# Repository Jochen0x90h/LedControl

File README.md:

# LED Control

Control unit for LED strips

## Features
* 128x64 OLED Display
* Support for presets, i.e. the same effect can be configured with different parameters in the preset list

## Compile
See README.md of coco base library

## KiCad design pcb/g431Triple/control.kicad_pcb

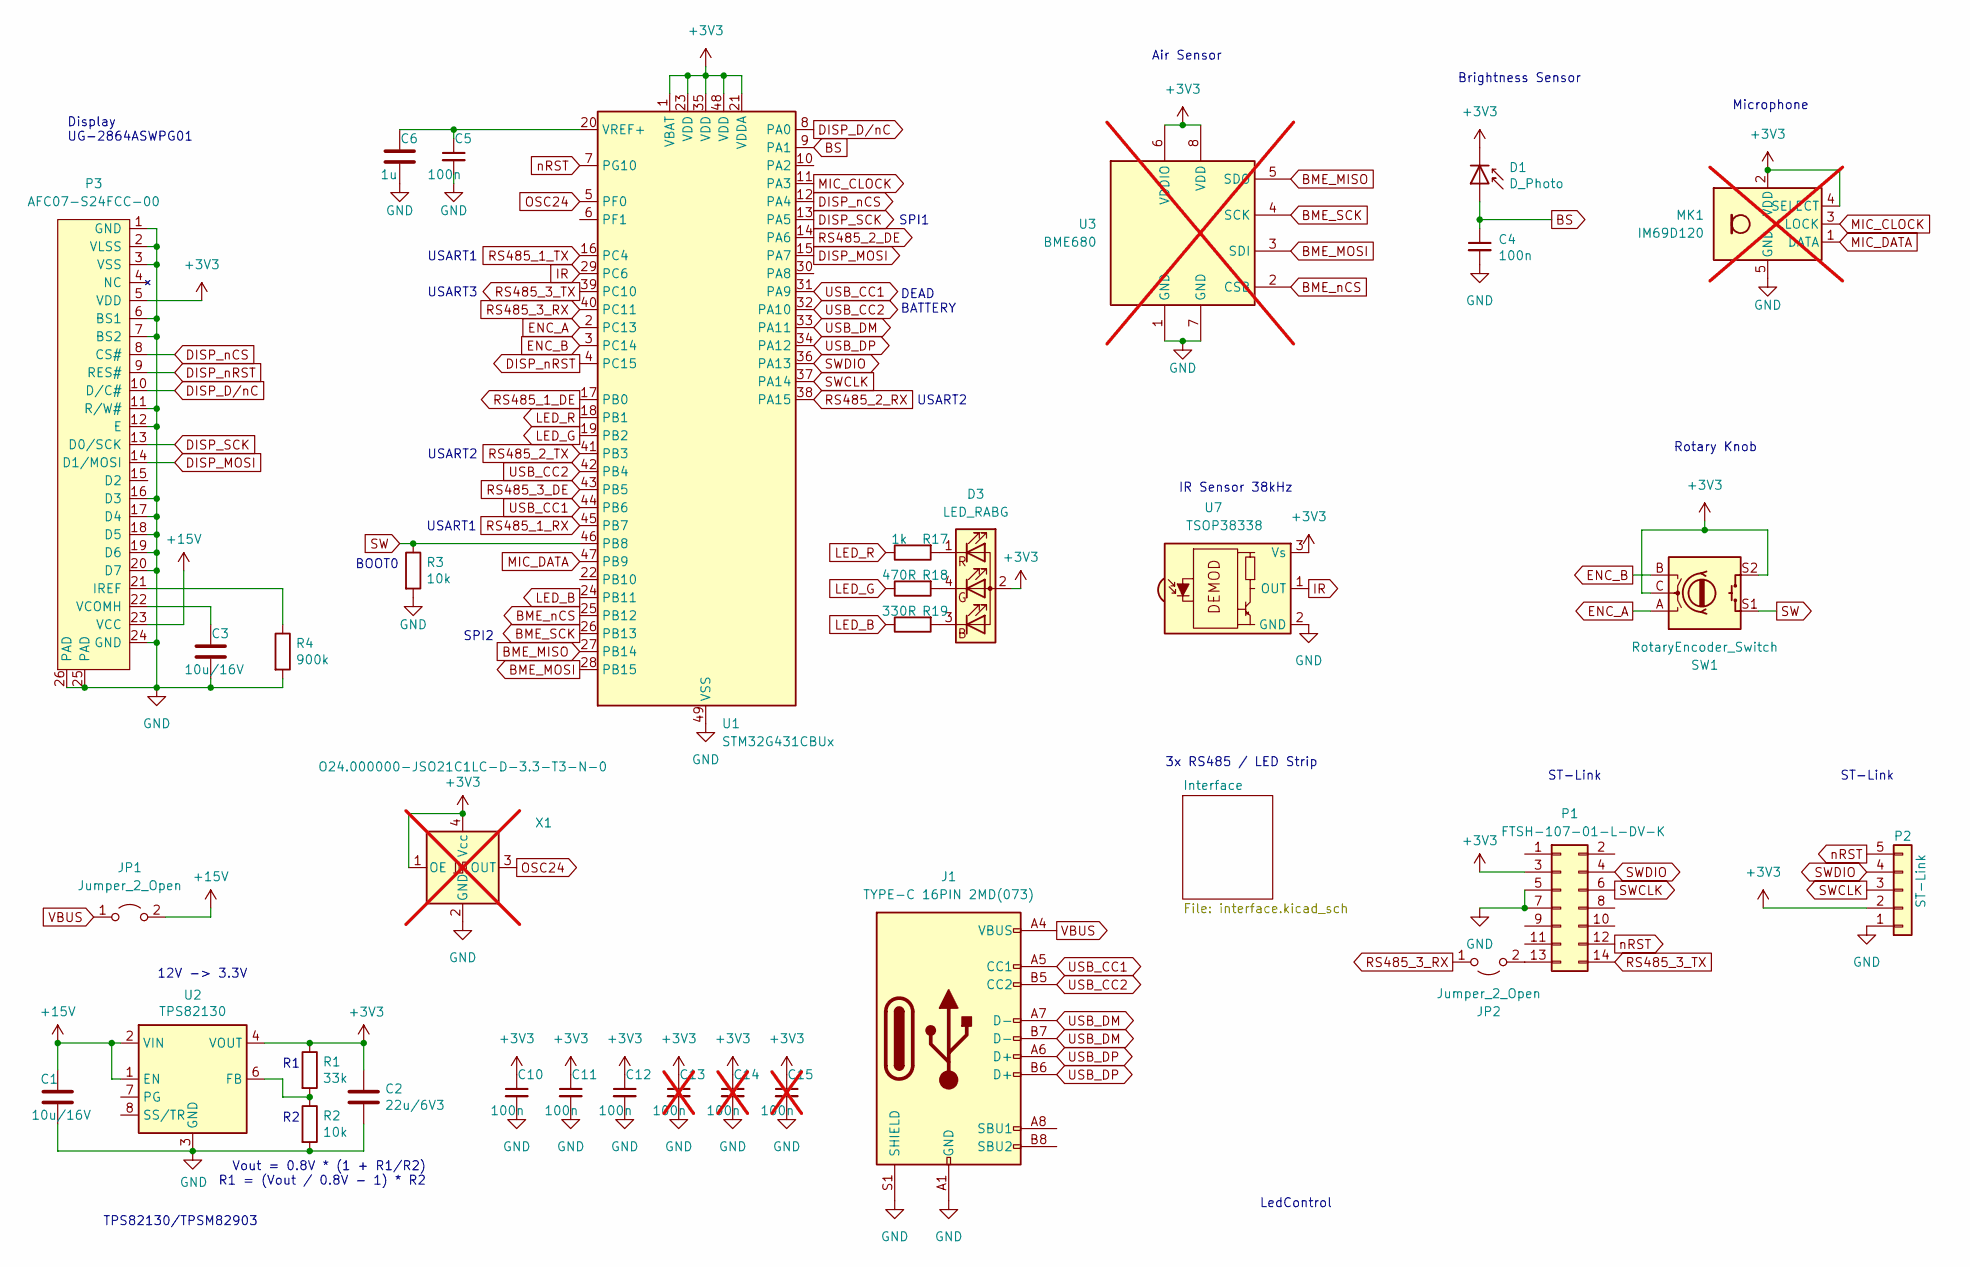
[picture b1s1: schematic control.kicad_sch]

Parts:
C1, C3: 10u/16V; 1206
C2: 22u/6V3; 0805
C4, C5, C10, C11, C12: 100n; 0603
C6: 1u; 0603
C13, C14, C15: 100n; 0603; not fitted
D1: D_Photo; PhotoDiode
D3: LED_RABG; LED_D5.0mm-4_RGB
J1: TYPE-C 16PIN 2MD(073); TYPE-C-16PIN-2MD-073
JP1, JP2: Jumper_2_Open; Jumper
MK1: IM69D120; Infineon_PG-LLGA-5-1; not fitted
P1: FTSH-107-01-L-DV-K; PinHeader-2x7-1.27mm-smd
P2: ST-Link; ProgPads
P3: AFC07-S24FCC-00; Connector-Flat-24-0.5mm
R1: 33k; 0603
R2, R3: 10k; 0603
R4: 900k; 0603
R17: 1k; 0603
R18: 470R; 0603
R19: 330R; 0603
SW1: RotaryEncoder_Switch; PEC12R-4217F-S0024
U1: STM32G431CBUx; STM32-UFQFPN48
U2: TPS82130
U3: BME680; not fitted
U7: TSOP38338
X1: O24.000000-JSO21C1LC-D-3.3-T3-N-0; JSO21; not fitted

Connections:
+3V3: C2.1, C10.1, C11.1, C12.1, C13.1, C14.1, C15.1, D1.1 (K), D3.2 (A), MK1.2 (VDD), MK1.4 (SELECT), P1.3, P2.2, P3.5 (VDD), R1.1, SW1.C, SW1.S2, U1.1 (VBAT), U1.21 (VDDA), U1.23 (VDD), U1.35 (VDD), U1.48 (VDD), U2.4 (VOUT), U2.5 (VOUT), U3.6 (VDDIO), U3.8 (VDD), U7.3 (Vs), X1.1 (OE), X1.4 (Vcc); also elsewhere on the board
+15V: C1.1, JP1.2 (B), P3.23 (VCC), U2.1 (EN), U2.2 (VIN); also elsewhere on the board
BME_MISO: U1.27 (PB14), U3.5 (SDO)
BME_MOSI: U1.28 (PB15), U3.3 (SDI)
BME_SCK: U1.26 (PB13), U3.4 (SCK)
BME_nCS: U1.25 (PB12), U3.2 (CSB)
BS: C4.1, D1.2 (A), U1.9 (PA1)
DISP_D/nC: P3.10 (D/C#), U1.8 (PA0)
DISP_MOSI: P3.14 (D1/MOSI), U1.15 (PA7)
DISP_SCK: P3.13 (D0/SCK), U1.13 (PA5)
DISP_nCS: P3.8 (CS#), U1.12 (PA4)
DISP_nRST: P3.9 (RES#), U1.4 (PC15)
ENC_A: SW1.A, U1.2 (PC13)
ENC_B: SW1.B, U1.3 (PC14)
GND: C1.2, C2.2, C3.2, C4.2, C5.2, C6.2, C10.2, C11.2, C12.2, C13.2, C14.2, C15.2, J1.A1 (GND), J1.A12 (GND), J1.B1 (GND), J1.B12 (GND), J1.S1 (SHIELD), MK1.5 (GND), P1.5, P1.7, P2.1, P3.1 (GND), P3.2 (VLSS), P3.3 (VSS), P3.6 (BS1), P3.7 (BS2), P3.11 (R/W#), P3.12 (E), P3.16 (D3), P3.17 (D4), P3.18 (D5), P3.19 (D6), P3.20 (D7), P3.24 (GND), P3.25 (PAD), P3.26 (PAD), R2.2, R3.2, R4.2, U1.49 (VSS), U2.3 (GND), U2.9 (GND), U3.1 (GND), U3.7 (GND), U7.2 (GND), X1.2 (GND); also elsewhere on the board
IR: U1.29 (PC6), U7.1 (OUT)
LED_B: R19.1, U1.24 (PB11)
LED_G: R18.1, U1.19 (PB2)
LED_R: R17.1, U1.18 (PB1)
MIC_CLOCK: MK1.3 (CLOCK), U1.11 (PA3)
MIC_DATA: MK1.1 (DATA), U1.47 (PB9)
unnamed: D3.3 (BK), R19.2
unnamed: D3.4 (GK), R18.2
unnamed: D3.1 (RK), R17.2
unnamed: JP2.2 (B), P1.13
unnamed: P3.21 (IREF), R4.1
unnamed: C3.1, P3.22 (VCOMH)
unnamed: C5.1, C6.1, U1.20 (VREF+)
unnamed: R1.2, R2.1, U2.6 (FB)
OSC24: U1.5 (PF0), X1.3 (OUT)
RS485_1_DE: U1.17 (PB0); also elsewhere on the board
RS485_1_RX: U1.45 (PB7); also elsewhere on the board
RS485_1_TX: U1.16 (PC4); also elsewhere on the board
RS485_2_DE: U1.14 (PA6); also elsewhere on the board
RS485_2_RX: U1.38 (PA15); also elsewhere on the board
RS485_2_TX: U1.41 (PB3); also elsewhere on the board
RS485_3_DE: U1.43 (PB5); also elsewhere on the board
RS485_3_RX: JP2.1 (A), U1.40 (PC11); also elsewhere on the board
RS485_3_TX: P1.14, U1.39 (PC10); also elsewhere on the board
SW: R3.1, SW1.S1, U1.46 (PB8)
SWCLK: P1.6, P2.3, U1.37 (PA14)
SWDIO: P1.4, P2.4, U1.36 (PA13)
USB_CC1: J1.A5 (CC1), U1.31 (PA9), U1.44 (PB6)
USB_CC2: J1.B5 (CC2), U1.32 (PA10), U1.42 (PB4)
USB_DM: J1.A7 (D-), J1.B7 (D-), U1.33 (PA11)
USB_DP: J1.A6 (D+), J1.B6 (D+), U1.34 (PA12)
VBUS: J1.A4 (VBUS), J1.A9 (VBUS), J1.B4 (VBUS), J1.B9 (VBUS), JP1.1 (A)
nRST: P1.12, P2.5, U1.7 (PG10)

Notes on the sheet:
12V -> 3.3V
BOOT0
SPI2
USART2
ST-Link
Vout = 0.8V * (1 + R1/R2) R1 = (Vout / 0.8V - 1) * R2
DEAD BATTERY
Display UG-2864ASWPG01
Air Sensor
USART3
Microphone
LedControl
3x RS485 / LED Strip
USART1
Brightness Sensor
TPS82130/TPSM82903
IR Sensor 38kHz
SPI1
Rotary Knob

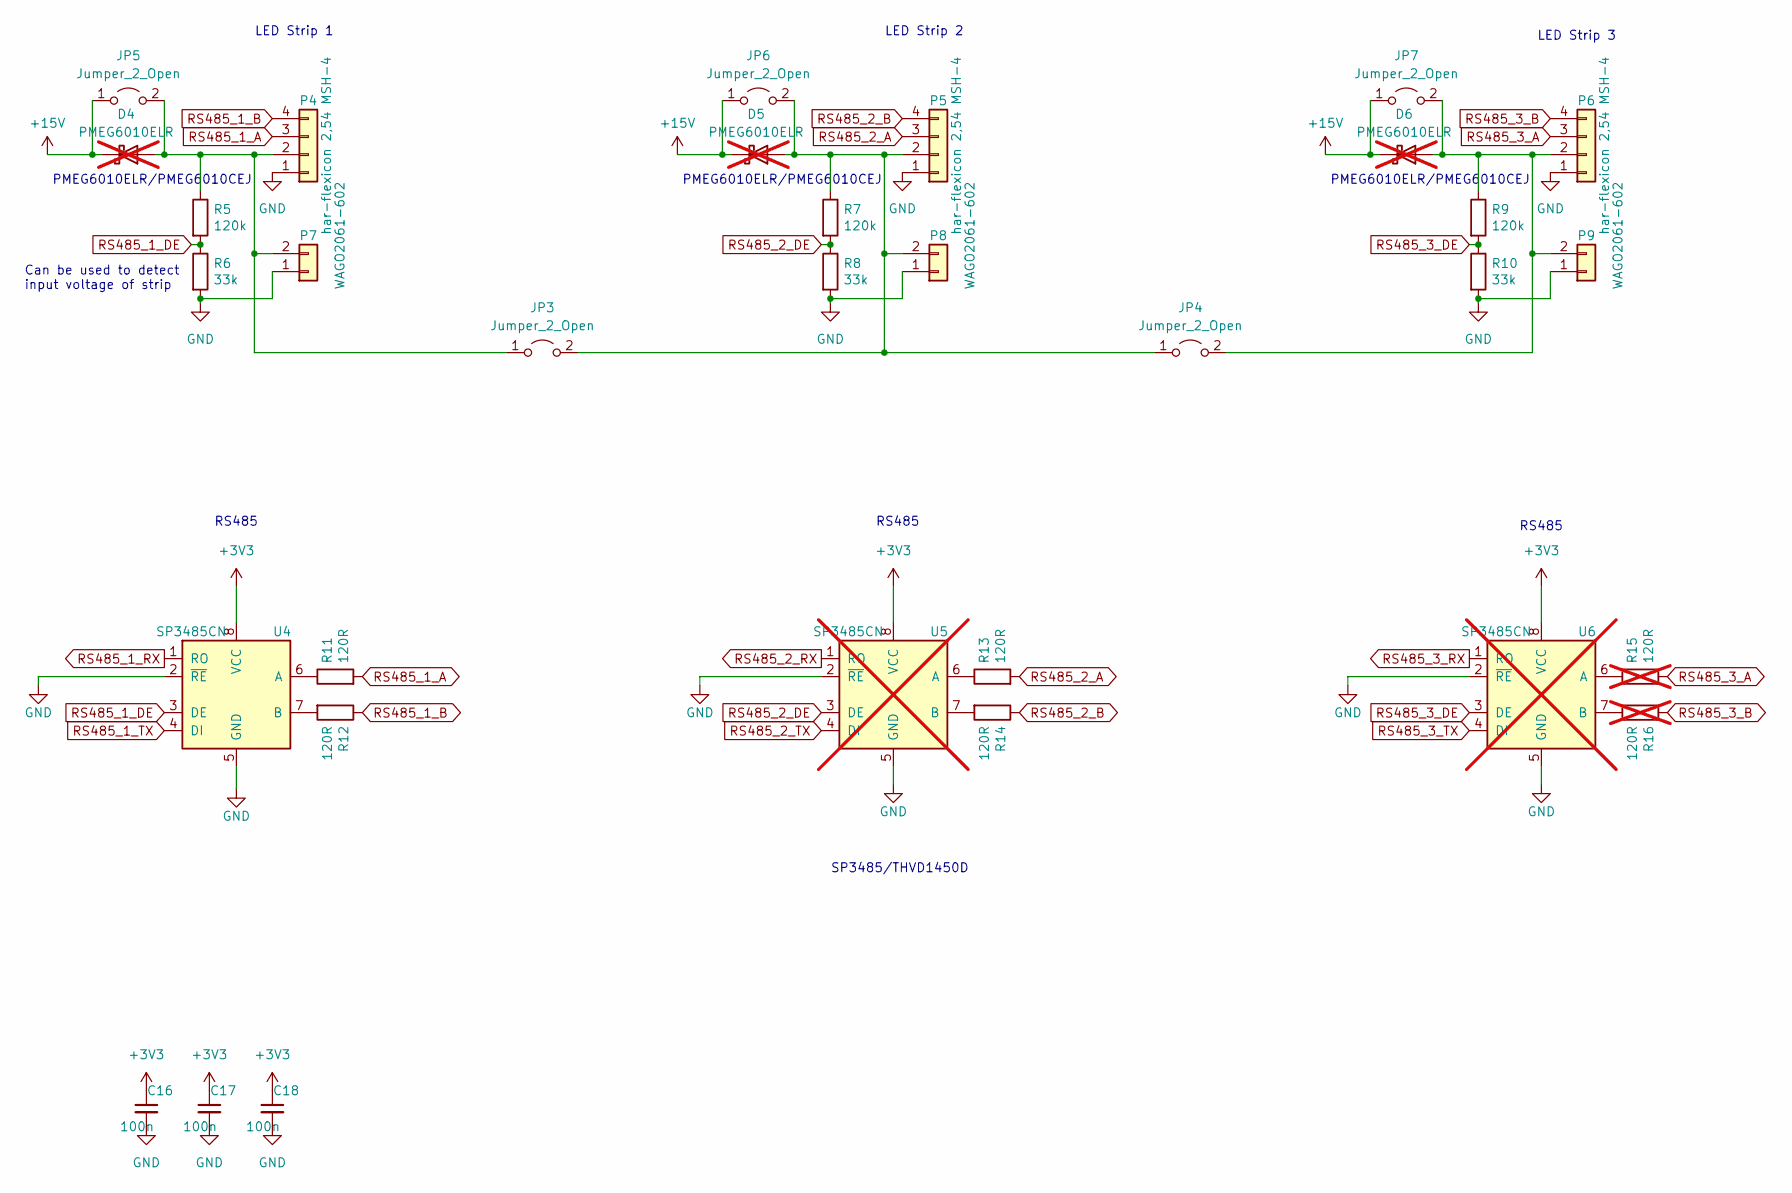
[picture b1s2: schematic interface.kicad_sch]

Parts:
C16, C17, C18: 100n; 0603
D4, D5, D6: PMEG6010ELR; not fitted
JP3, JP4, JP5, JP6, JP7: Jumper_2_Open; Jumper
P4, P5, P6: har-flexicon 2,54 MSH-4; Harting14110413002000
P7, P8, P9: WAGO2061-602
R5, R7, R9: 120k; 0603
R6, R8, R10: 33k; 0603
R11, R12, R13, R14: 120R; 1206-term
R15, R16: 120R; 1206-term; not fitted
U4: SP3485CN; SO-8
U5, U6: SP3485CN; SO-8; not fitted

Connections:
+3V3: C16.1, C17.1, C18.1, U4.8 (VCC), U5.8 (VCC), U6.8 (VCC); also elsewhere on the board
+15V: D4.1 (K), D5.1 (K), D6.1 (K), JP5.1 (A), JP6.1 (A), JP7.1 (A); also elsewhere on the board
GND: C16.2, C17.2, C18.2, P4.1, P5.1, P6.1, P7.1, P8.1, P9.1, R6.2, R8.2, R10.2, U4.2 (~RE), U4.5 (GND), U5.2 (~RE), U5.5 (GND), U6.2 (~RE), U6.5 (GND); also elsewhere on the board
unnamed: D4.2 (A), JP3.1 (A), JP5.2 (B), P4.2, P7.2, R5.1
unnamed: D5.2 (A), JP3.2 (B), JP4.1 (A), JP6.2 (B), P5.2, P8.2, R7.1
unnamed: D6.2 (A), JP4.2 (B), JP7.2 (B), P6.2, P9.2, R9.1
unnamed: R11.1, U4.6 (A)
unnamed: R12.2, U4.7 (B)
unnamed: R13.1, U5.6 (A)
unnamed: R14.2, U5.7 (B)
unnamed: R15.1, U6.6 (A)
unnamed: R16.2, U6.7 (B)
RS485_1_A: P4.3, R11.2
RS485_1_B: P4.4, R12.1
RS485_1_DE: R5.2, R6.1, U4.3 (DE); also elsewhere on the board
RS485_1_RX: U4.1 (RO); also elsewhere on the board
RS485_1_TX: U4.4 (DI); also elsewhere on the board
RS485_2_A: P5.3, R13.2
RS485_2_B: P5.4, R14.1
RS485_2_DE: R7.2, R8.1, U5.3 (DE); also elsewhere on the board
RS485_2_RX: U5.1 (RO); also elsewhere on the board
RS485_2_TX: U5.4 (DI); also elsewhere on the board
RS485_3_A: P6.3, R15.2
RS485_3_B: P6.4, R16.1
RS485_3_DE: R9.2, R10.1, U6.3 (DE); also elsewhere on the board
RS485_3_RX: U6.1 (RO); also elsewhere on the board
RS485_3_TX: U6.4 (DI); also elsewhere on the board

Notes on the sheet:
Can be used to detect input voltage of strip
LED Strip 3
PMEG6010ELR/PMEG6010CEJ
LED Strip 1
SP3485/THVD1450D
LED Strip 2
RS485

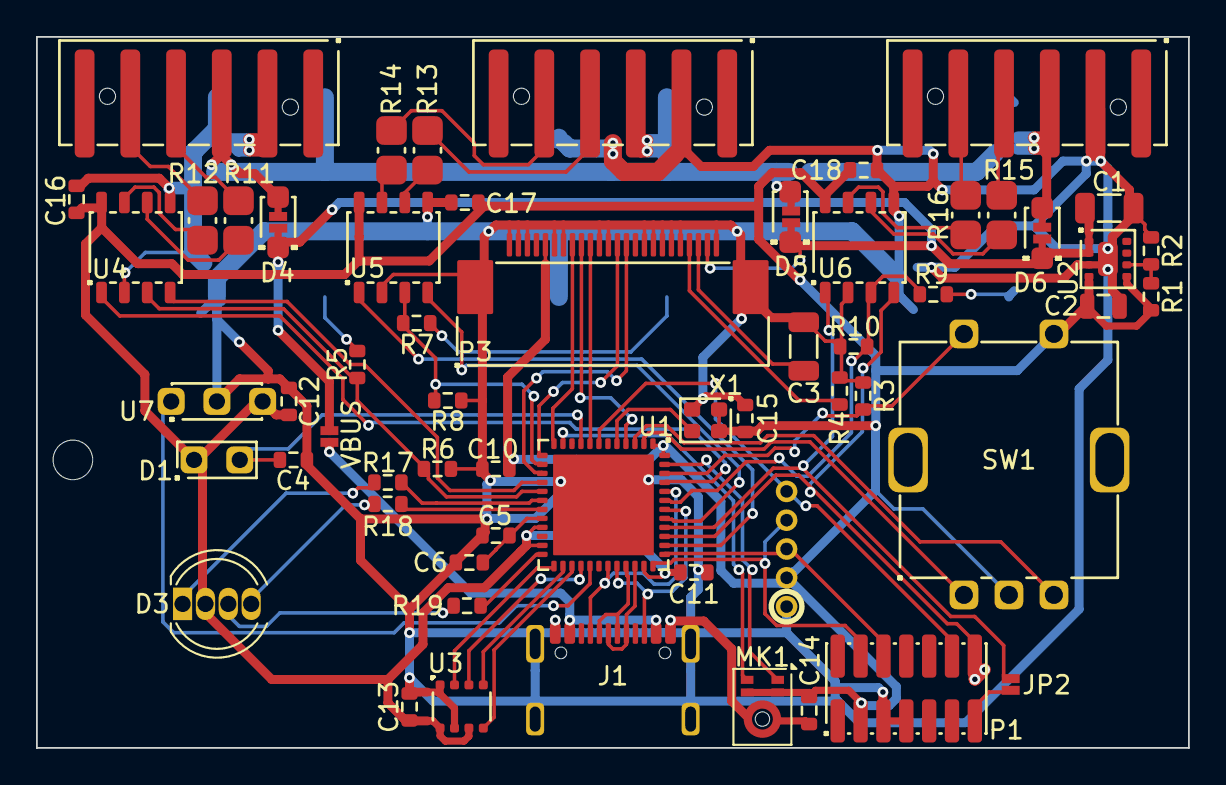
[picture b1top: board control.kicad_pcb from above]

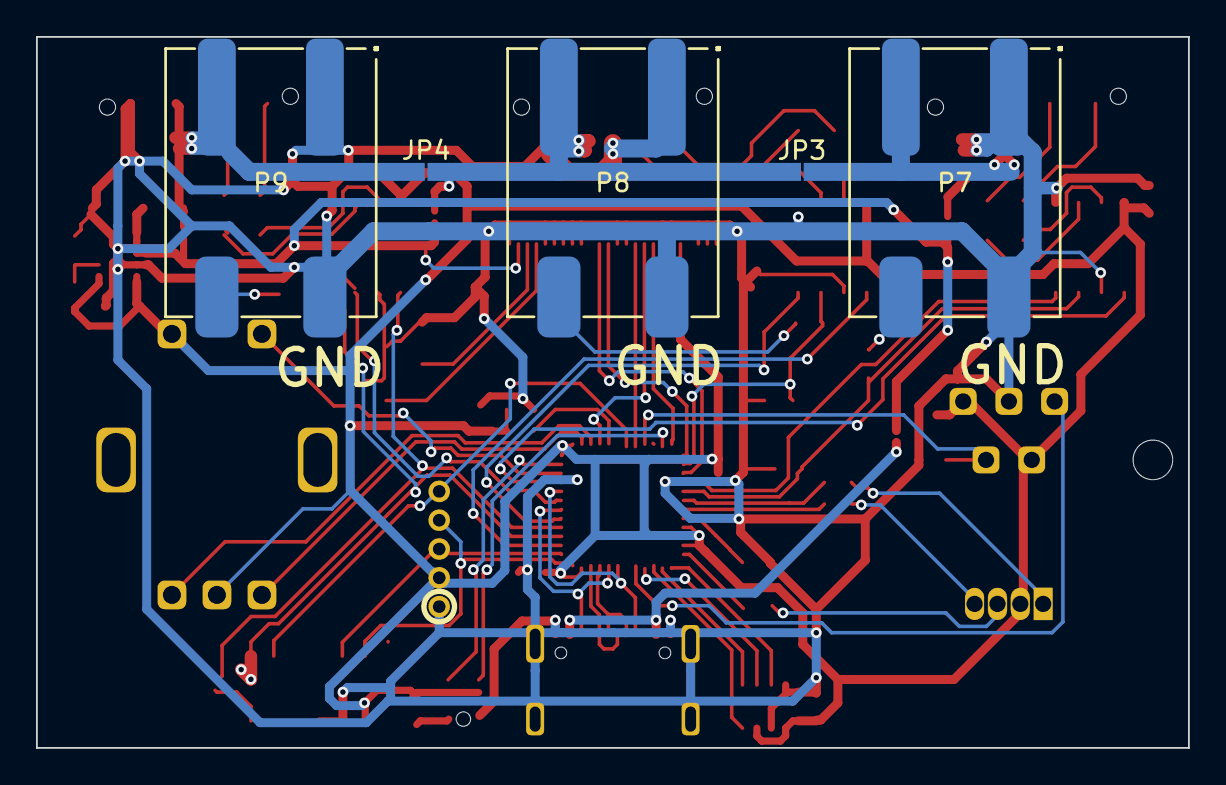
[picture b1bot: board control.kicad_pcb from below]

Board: 2 copper layers, 64.0 x 39.5 mm, 66 parts (6 on the bottom side), 63 nets.

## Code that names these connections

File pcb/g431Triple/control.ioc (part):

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Mcu.Name=STM32G431C(6-8-B)Ux
Mcu.Package=UFQFPN48
Mcu.UserName=STM32G431CBUx
PA0.GPIOParameters=GPIO_Label
PA0.GPIO_Label=DISP_D/C\#
PA0.Signal=GPIO_Output
PA1.Mode=INP
PA1.Signal=COMP1_INP
PA10.Mode=EnableDeadBattery
PA10.Signal=UCPD1_DBCC2
PA11.Mode=Device
PA11.Signal=USB_DM
PA12.Mode=Device
PA12.Signal=USB_DP
PA13.Mode=Serial_Wire
PA13.Signal=SYS_JTMS-SWDIO
PA14.Mode=Serial_Wire
PA14.Signal=SYS_JTCK-SWCLK
PA15.Mode=Asynchronous
PA15.Signal=USART2_RX
PA2.Mode=Follower-DAC_OUT2-INP
PA2.Signal=OPAMP1_VOUT
PA3.Signal=SAI1_CK1
PA4.GPIOParameters=GPIO_Label
PA4.GPIO_Label=DISP_CS
PA4.Signal=GPIO_Output
PA5.Mode=TX_Only_Simplex_Unidirect_Master
PA5.Signal=SPI1_SCK
PA6.GPIOParameters=GPIO_Label
PA6.GPIO_Label=RS485_2_DE
PA6.Signal=GPIO_Output
PA7.Mode=TX_Only_Simplex_Unidirect_Master
PA7.Signal=SPI1_MOSI
PA9.Mode=EnableDeadBattery
PA9.Signal=UCPD1_DBCC1
PB0.GPIOParameters=GPIO_Label
PB0.GPIO_Label=RS485_DE
PB0.Signal=GPIO_Output
PB1.Mode=Standalone-DAC_OUT2-INP
PB1.Signal=OPAMP3_VOUT
PB12.GPIOParameters=GPIO_Label
PB12.GPIO_Label=BME_CS
PB12.Signal=GPIO_Output
PB13.Mode=Full_Duplex_Master
PB13.Signal=SPI2_SCK
PB14.Mode=Full_Duplex_Master
PB14.Signal=SPI2_MISO
PB15.Mode=Full_Duplex_Master
PB15.Signal=SPI2_MOSI
PB2.Mode=Standalone-DAC_OUT2-INP
PB2.Signal=OPAMP3_VINM
PB3.Mode=Asynchronous
PB3.Signal=USART2_TX
PB4.Mode=Sink_AllSignals
PB4.Signal=UCPD1_CC2
PB5.GPIOParameters=GPIO_Label
PB5.GPIO_Label=RS485_3_DE
PB5.Signal=GPIO_Output
PB6.Mode=Sink_AllSignals
PB6.Signal=UCPD1_CC1
PB7.Mode=Asynchronous
PB7.Signal=USART1_RX
PB8-BOOT0.GPIOParameters=GPIO_Label
PB8-BOOT0.GPIO_Label=SW
PB8-BOOT0.Signal=GPIO_Input
PB9.Signal=SAI1_D2
PC10.Mode=Asynchronous
PC10.Signal=USART3_TX
PC11.Mode=Asynchronous
PC11.Signal=USART3_RX
PC13.GPIOParameters=GPIO_Label
PC13.GPIO_Label=ENC_A
PC13.Signal=GPIO_Input
PC14-OSC32_IN.GPIOParameters=GPIO_Label
PC14-OSC32_IN.GPIO_Label=ENC_B
PC14-OSC32_IN.Signal=GPIO_Input
PC15-OSC32_OUT.GPIOParameters=GPIO_Label
PC15-OSC32_OUT.GPIO_Label=DISP_RESET
PC15-OSC32_OUT.Signal=GPIO_Output
PC4.Mode=Asynchronous
PC4.Signal=USART1_TX
PC6.Signal=S_TIM3_CH1
PG10-NRST.GPIOParameters=GPIO_Label
PG10-NRST.GPIO_Label=nRST
PG10-NRST.Signal=GPIO_Input
RCC.HSE_VALUE=8000000
RCC.SYSCLKFreq_VALUE=160000000
RCC.SYSCLKSource=RCC_SYSCLKSOURCE_PLLCLK
board=custom

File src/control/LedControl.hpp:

#pragma once

#include "config.hpp"
#include <coco/platform/Flash_FLASH.hpp>
#include <coco/platform/LedStrip_UART_DMA.hpp>
#include <coco/platform/SpiMaster_SPI_DMA.hpp>
#include <coco/platform/InputDevice_EXTI_TIM.hpp>
#include <coco/platform/OutputPort_GPIO.hpp>
#include <coco/platform/Loop_TIM2.hpp>
#include <coco/BufferStorage.hpp>
#include <coco/SSD130x.hpp>
#include <coco/platform/platform.hpp>
#include <coco/platform/gpio.hpp>


using namespace coco;
using namespace coco::literals;

constexpr int DISPLAY_WIDTH = 128;
constexpr int DISPLAY_HEIGHT = 64;
constexpr SSD130x::Flags DISPLAY_FLAGS = SSD130x::Flags::UG_2864ASWPG01_SPI;

constexpr int LEDSTRIP_LENGTH = 300;

// flash
constexpr int PAGE_SIZE = Flash_FLASH::PAGE_SIZE;
constexpr int BLOCK_SIZE = Flash_FLASH::BLOCK_SIZE;
constexpr int SECTOR_COUNT = 4;
constexpr int SECTOR_PAGE_COUNT = FLASH_SIZE / (2 * PAGE_SIZE * SECTOR_COUNT); // use half of available flash which is 64K, also configure in link.ld
constexpr int SECTOR_SIZE = SECTOR_PAGE_COUNT * PAGE_SIZE;
constexpr BufferStorage::Info storageInfo {
	FLASH_ADDRESS + FLASH_SIZE - SECTOR_COUNT * SECTOR_SIZE, // address
	BLOCK_SIZE,
	PAGE_SIZE,
	SECTOR_SIZE,
	SECTOR_COUNT,
	BufferStorage::Type::MEM_4N
};


// drivers for LedControl
struct Drivers {
	Loop_TIM2 loop{APB1_TIMER_CLOCK};

	// LED strip
	using LedStrip = LedStrip_UART_DMA;
	LedStrip ledStrip{loop,
		gpio::Config::PC4 | gpio::Config::AF7 | gpio::Config::SPEED_HIGH, // USART1 TX (RS485_TX)
		usart::USART1_INFO,
		dma::DMA1_CH1_INFO,
		USART1_CLOCK,
		1125ns, // bit time T
		75us}; // reset time
	LedStrip::Buffer<LEDSTRIP_LENGTH * 3> buffer1{ledStrip};
	LedStrip::Buffer<LEDSTRIP_LENGTH * 3> buffer2{ledStrip};

	// display
	using SpiMaster = SpiMaster_SPI_DMA;
	SpiMaster displaySpi{loop,
		gpio::Config::PA5 | gpio::Config::AF5, // SPI1 SCK (DISP_SCK)
		gpio::Config::NONE, // no MISO, send only
		gpio::Config::PA7 | gpio::Config::AF5, // SPI1 MOSI (DISP_MOSI)
		gpio::Config::PA0, // DC (DISP_D/nC)
		spi::SPI1_INFO,
		dma::DMA1_CH2_CH3_INFO,
		spi::Config::CLOCK_DIV32 | spi::Config::PHA1_POL1};
	SpiMaster::Channel displayChannel{displaySpi, gpio::Config::PA4 | gpio::Config::INVERT, true}; // nCS (DISP_nCS)
	SpiMaster::Buffer<DISPLAY_WIDTH * DISPLAY_HEIGHT / 8> displayBuffer{displayChannel};

	// display reset pin
	static constexpr OutputPort_GPIO::Config outputConfig[] {
		{gpio::Config::PA2 | gpio::Config::SPEED_MEDIUM | gpio::Config::INVERT, false}, // display reset (DISP_nRST)
	};
	OutputPort_GPIO resetPin{outputConfig};

	// display reset method
	AwaitableCoroutine resetDisplay() {
		resetPin.set(1, 1);
		co_await loop.sleep(10ms);
		resetPin.set(0, 1);
		co_return;
	}

	// rotary knob with push button
	using InputDevice = InputDevice_EXTI_TIM;
	static constexpr gpio::Config inputPinConfigs[] {
		gpio::Config::PC13 | gpio::Config::PULL_DOWN, // rotary knob A (ENC_A)
		gpio::Config::PC14 | gpio::Config::PULL_DOWN, // rotary knob B (ENC_B)
		gpio::Config::PC15 | gpio::Config::PULL_DOWN, // push button (SW)
	};
	static constexpr InputDevice::Config inputConfigs[] {
		{0, 0, InputDevice::Action::DECREMENT_WHEN_ENABLED, InputDevice::Action::INCREMENT_WHEN_ENABLED, 1ms, 1ms}, // quadrature decoder (inputs 0 and 1, counter 0)
		{2, 1, InputDevice::Action::INCREMENT, InputDevice::Action::NONE, 10ms, 10ms}, // button press (input 2, counter 1)
		{2, 2, InputDevice::Action::INCREMENT, InputDevice::Action::NONE, 3s, 10ms}, // button long press (input 2, counter 2)
	};
	InputDevice input{loop,
		inputPinConfigs,
		inputConfigs,
		timer::TIM3_INFO,
		APB1_TIMER_CLOCK,
		0}; // CC index

	// flash
	Flash_FLASH::Buffer<256> flashBuffer;

	Drivers() {
		// set RS485_DE high
		gpio::configureOutput(gpio::Config::PB0, true);
	}
};

Drivers drivers;

extern "C" {

// LED strip
void USART1_IRQHandler() {
	drivers.ledStrip.UART_IRQHandler();
}
void DMA1_Channel1_IRQHandler() {
	drivers.ledStrip.DMA_IRQHandler();
}

// display
void DMA1_Channel2_IRQHandler() {
	drivers.displaySpi.DMA_Rx_IRQHandler();
}

// rotary knob with push button
void EXTI15_10_IRQHandler() {
    drivers.input.EXTI_IRQHandler();
}
void TIM3_IRQHandler() {
    drivers.input.TIM_IRQHandler();
}

}

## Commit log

2024-10-03 Cleanup, add casing
2024-11-11 Add IR receiver
2024-12-22 Control brightness and duraton with remote control
2025-01-26 Add SnowSparkle, new footprints
2025-04-14 Use TSOP38338
2025-05-01 Rename to g431/g431Triple, new pin ordering for Harting connector
2025-05-24 Multiple led strips
2025-06-16 Add color temperature
2025-10-05 Start preset name editor
2025-10-20 Display preset names
2026-03-05 Works on g431Triple
